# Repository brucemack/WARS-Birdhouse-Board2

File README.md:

Connector J1
============

Right Column
* 1: 3.3V out, used for onboard SX1276 module, but could also be used to power MCU.
* 3: Raw panel input, not used for anything on board *except* panel sense.
* 5: Raw panel input, could be used for charge controller IN+.
* 7: 4-6V supply in, could be taken from charge controller OUT+.
* 9: Panel sense out, could be sent to ADC for monitoring.
* 11: 4-6V supply sense out, could bne sent to ADC for monitoring.
* 13: GND (i.e. panel ground)
* 15: GND (i.e. charge controller OUT-)

Left Column
* 2: Radio interrupt out
* 4: Radio reset in
* 6: Radio SPI CS in
* 8: Radio SPI SCK in 
* 10: Radio SPI MOSI in
* 12: Radio SPI MISO out 
* 14: GND
* 16: GND

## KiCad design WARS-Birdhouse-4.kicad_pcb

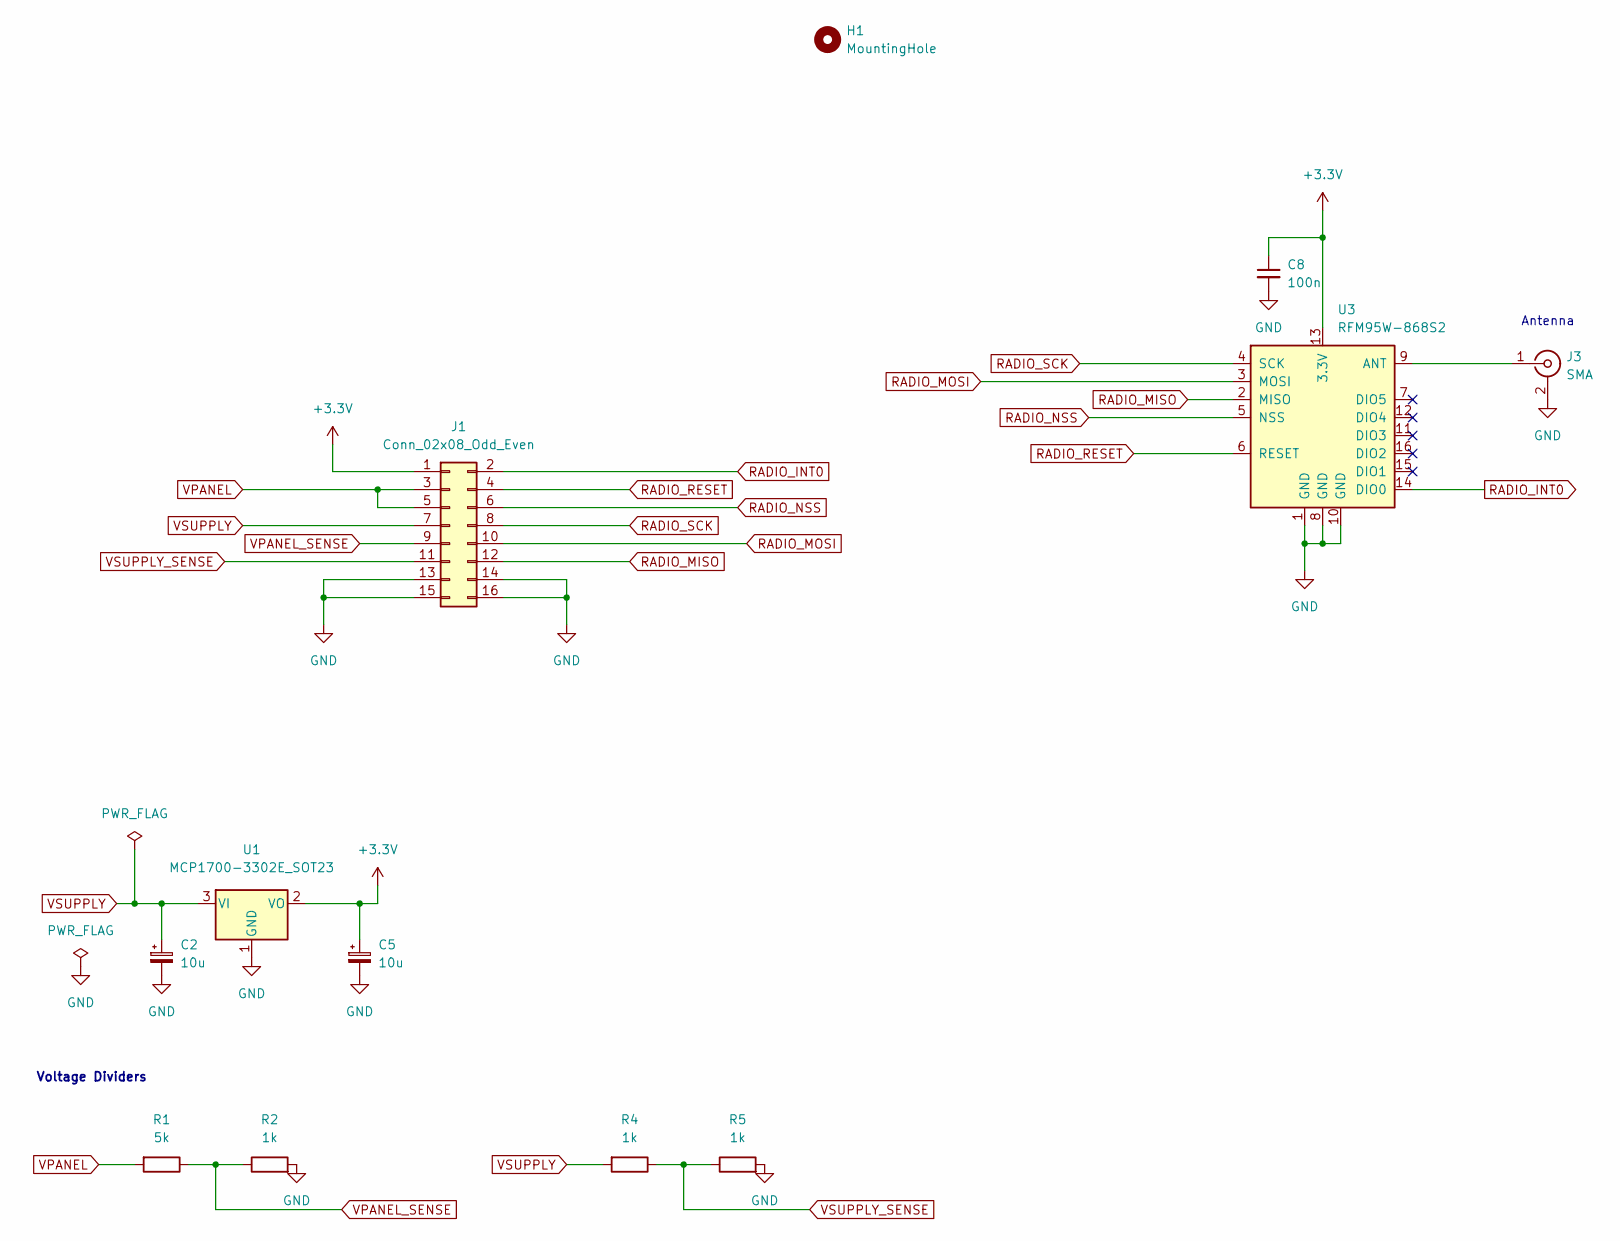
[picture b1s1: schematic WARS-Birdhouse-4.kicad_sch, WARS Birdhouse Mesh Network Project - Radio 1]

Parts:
C2, C5: 10u; CP_Elec_4x5.4
C8: 100n; C_0805_2012Metric_Pad1.18x1.45mm_HandSolder
H1: MountingHole; MountingHole_4mm
J1: Conn_02x08_Odd_Even; PinSocket_2x08_P2.54mm_Vertical
J3: SMA; SMA_Amphenol_132134_Vertical
R1: 5k; R_0805_2012Metric_Pad1.20x1.40mm_HandSolder
R2, R4, R5: 1k; R_0805_2012Metric_Pad1.20x1.40mm_HandSolder
U1: MCP1700-3302E_SOT23; SOT-23
U3: RFM95W-868S2; HOPERF_RFM9XW_SMD

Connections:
+3V3: C5.1, C8.1, J1.1, U1.2 (VO), U3.13 (3.3V)
GND: C2.2, C5.2, C8.2, J1.13, J1.14, J1.15, J1.16, J3.2 (Ext), R2.2, R5.2, U1.1 (GND), U3.1 (GND), U3.8 (GND), U3.10 (GND)
unnamed: J3.1 (In), U3.9 (ANT)
RADIO_INT0: J1.2, U3.14 (DIO0)
RADIO_MISO: J1.12, U3.2 (MISO)
RADIO_MOSI: J1.10, U3.3 (MOSI)
RADIO_NSS: J1.6, U3.5 (NSS)
RADIO_RESET: J1.4, U3.6 (RESET)
RADIO_SCK: J1.8, U3.4 (SCK)
VPANEL: J1.3, J1.5, R1.2
VPANEL_SENSE: J1.9, R1.1, R2.1
VSUPPLY: C2.1, J1.7, R4.2, U1.3 (VI)
VSUPPLY_SENSE: J1.11, R4.1, R5.1

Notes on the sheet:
Antenna
Voltage Dividers

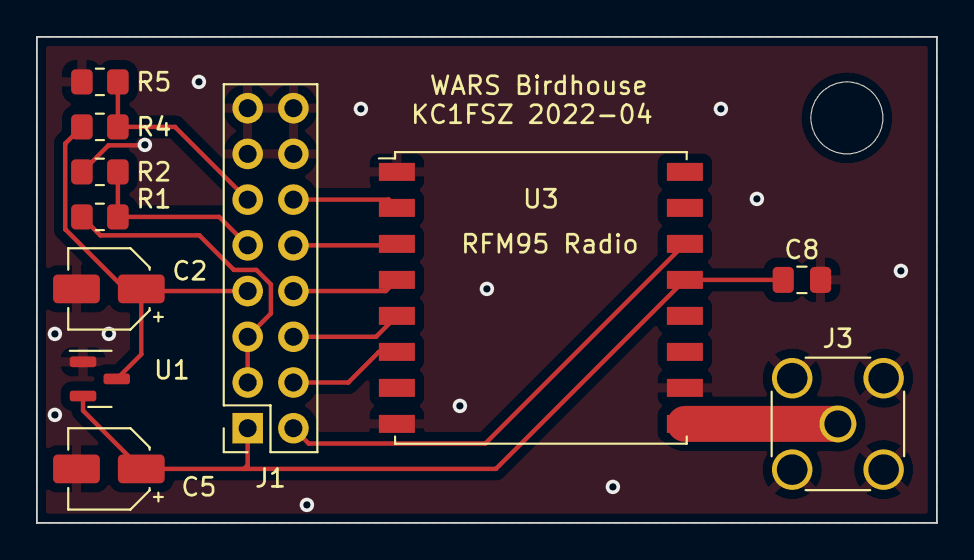
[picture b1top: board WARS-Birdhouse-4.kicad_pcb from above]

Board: 2 copper layers, 50.0 x 27.0 mm, 12 parts (0 on the bottom side), 13 nets.

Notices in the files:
WARS-Birdhouse-4.kicad_sch:
COPYRIGHT (C) 2022 - Bruce MacKinnon
